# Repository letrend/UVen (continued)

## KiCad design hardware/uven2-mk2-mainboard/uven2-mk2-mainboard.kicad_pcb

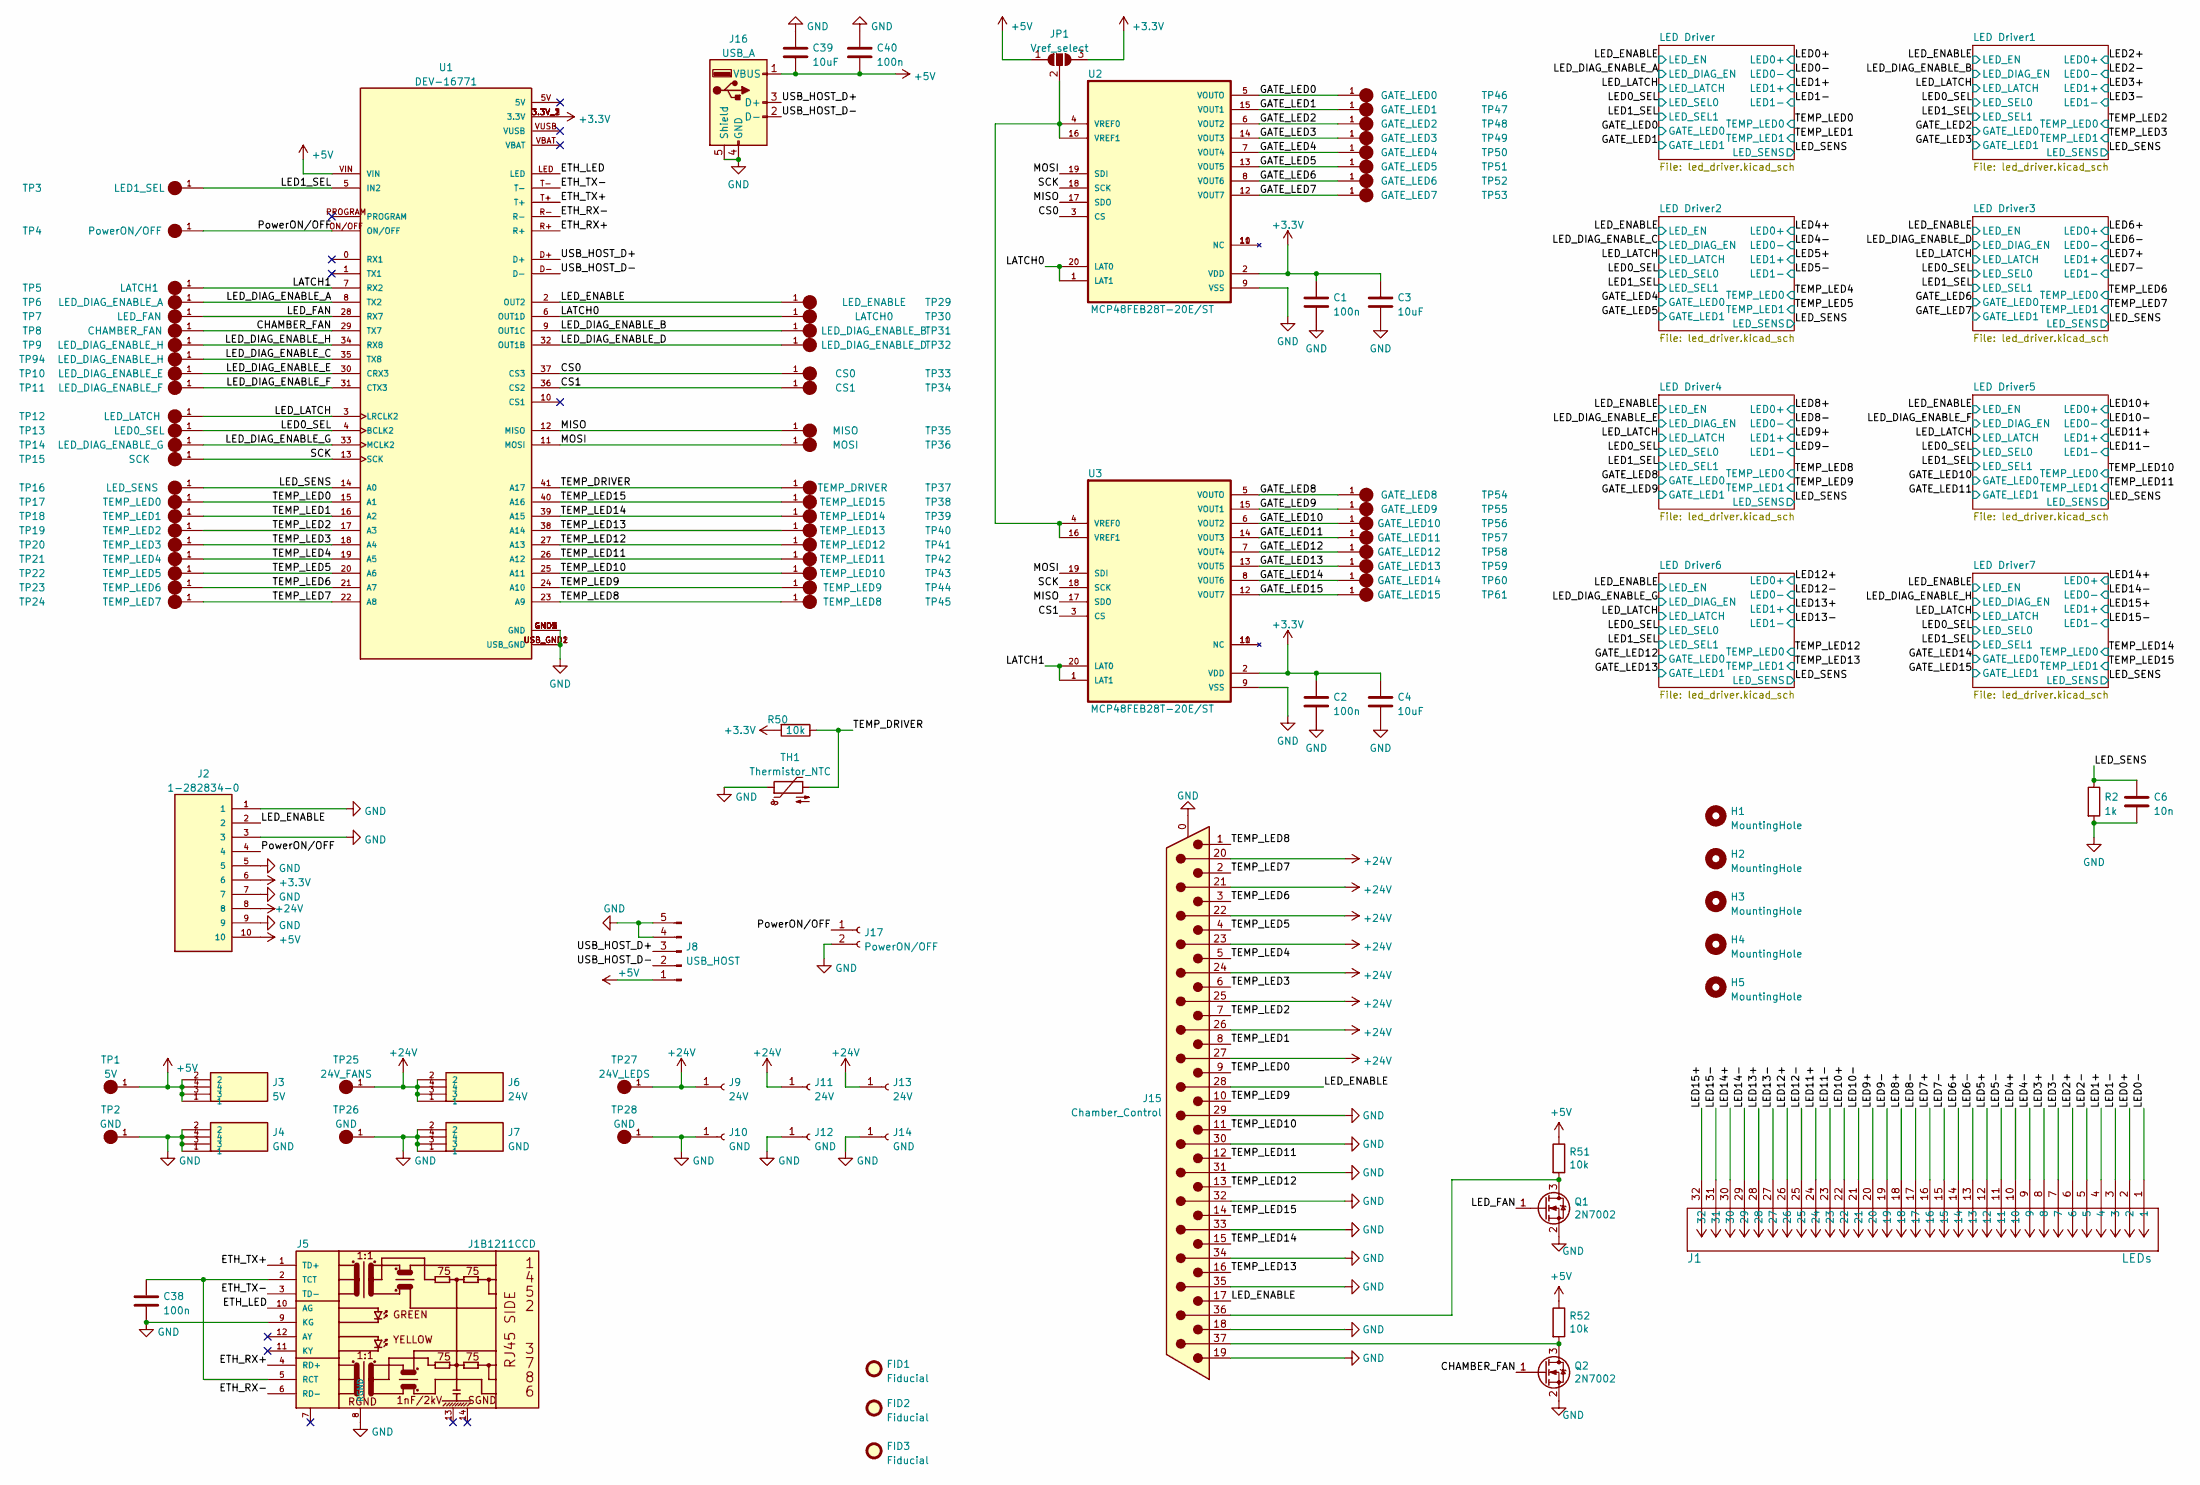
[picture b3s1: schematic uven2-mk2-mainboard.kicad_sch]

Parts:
C1, C2, C38, C40: 100n; C_0603_1608Metric_Pad1.08x0.95mm_HandSolder
C3, C4, C39: 10uF; C_0603_1608Metric_Pad1.08x0.95mm_HandSolder
C6: 10n; C_0603_1608Metric_Pad1.08x0.95mm_HandSolder
FID1, FID2, FID3: Fiducial; Fiducial_1mm_Dia_2.54mm_Outer_CopperTop
H1, H2, H3, H4, H5: MountingHole; MountingHole_3.2mm_M3
J1: LEDs; CONN_713-1436&slash_037-000_WAG
J2: 1-282834-0; TE_1-282834-0
J3: 5V; KEYSTONE_7767; PARTREV B
J4, J7: GND; KEYSTONE_7767; PARTREV B
J5: J1B1211CCD
J6: 24V; KEYSTONE_7767; PARTREV B
J8: USB_HOST; PinHeader_1x05_P2.54mm_Vertical
J9, J11, J13: 24V; 7466205R
J10, J12, J14: GND; 7466205R
J15: Chamber_Control; DSUB-37_Female_Horizontal_P2.77x2.84mm_EdgePinOffset7.70mm_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
J16: USB_A; USB_A_Molex_67643_Horizontal
J17: PowerON/OFF; PinHeader_1x02_P2.54mm_Vertical
JP1: Vref_select; SolderJumper-3_P1.3mm_Open_RoundedPad1.0x1.5mm_NumberLabels
Q1, Q2: 2N7002; SOT-23
R2: 1k; R_0603_1608Metric_Pad0.98x0.95mm_HandSolder
R50, R51, R52: 10k; R_0603_1608Metric_Pad0.98x0.95mm_HandSolder
TH1: Thermistor_NTC; R_0805_2012Metric_Pad1.20x1.40mm_HandSolder
TP1: 5V; TP420X150; PARTREV 1/06/14
TP2, TP26, TP28: GND; TP420X150; PARTREV 1/06/14
TP3: LED1_SEL; TP420X150; PARTREV 1/06/14
TP4: PowerON/OFF; TP420X150; PARTREV 1/06/14
TP5: LATCH1; TP420X150; PARTREV 1/06/14
TP6: LED_DIAG_ENABLE_A; TP420X150; PARTREV 1/06/14
TP7: LED_FAN; TP420X150; PARTREV 1/06/14
TP8: CHAMBER_FAN; TP420X150; PARTREV 1/06/14
TP9, TP94: LED_DIAG_ENABLE_H; TP420X150; PARTREV 1/06/14
TP10: LED_DIAG_ENABLE_E; TP420X150; PARTREV 1/06/14
TP11: LED_DIAG_ENABLE_F; TP420X150; PARTREV 1/06/14
TP12: LED_LATCH; TP420X150; PARTREV 1/06/14
TP13: LED0_SEL; TP420X150; PARTREV 1/06/14
TP14: LED_DIAG_ENABLE_G; TP420X150; PARTREV 1/06/14
TP15: SCK; TP420X150; PARTREV 1/06/14
TP16: LED_SENS; TP420X150; PARTREV 1/06/14
TP17: TEMP_LED0; TP420X150; PARTREV 1/06/14
TP18: TEMP_LED1; TP420X150; PARTREV 1/06/14
TP19: TEMP_LED2; TP420X150; PARTREV 1/06/14
TP20: TEMP_LED3; TP420X150; PARTREV 1/06/14
TP21: TEMP_LED4; TP420X150; PARTREV 1/06/14
TP22: TEMP_LED5; TP420X150; PARTREV 1/06/14
TP23: TEMP_LED6; TP420X150; PARTREV 1/06/14
TP24: TEMP_LED7; TP420X150; PARTREV 1/06/14
TP25: 24V_FANS; TP420X150; PARTREV 1/06/14
TP27: 24V_LEDS; TP420X150; PARTREV 1/06/14
TP29: LED_ENABLE; TP420X150; PARTREV 1/06/14
TP30: LATCH0; TP420X150; PARTREV 1/06/14
TP31: LED_DIAG_ENABLE_B; TP420X150; PARTREV 1/06/14
TP32: LED_DIAG_ENABLE_D; TP420X150; PARTREV 1/06/14
TP33: CS0; TP420X150; PARTREV 1/06/14
TP34: CS1; TP420X150; PARTREV 1/06/14
TP35: MISO; TP420X150; PARTREV 1/06/14
TP36: MOSI; TP420X150; PARTREV 1/06/14
TP37: TEMP_DRIVER; TP420X150; PARTREV 1/06/14
TP38: TEMP_LED15; TP420X150; PARTREV 1/06/14
TP39: TEMP_LED14; TP420X150; PARTREV 1/06/14
TP40: TEMP_LED13; TP420X150; PARTREV 1/06/14
TP41: TEMP_LED12; TP420X150; PARTREV 1/06/14
TP42: TEMP_LED11; TP420X150; PARTREV 1/06/14
TP43: TEMP_LED10; TP420X150; PARTREV 1/06/14
TP44: TEMP_LED9; TP420X150; PARTREV 1/06/14
TP45: TEMP_LED8; TP420X150; PARTREV 1/06/14
TP46: GATE_LED0; TP420X150; PARTREV 1/06/14
TP47: GATE_LED1; TP420X150; PARTREV 1/06/14
TP48: GATE_LED2; TP420X150; PARTREV 1/06/14
TP49: GATE_LED3; TP420X150; PARTREV 1/06/14
TP50: GATE_LED4; TP420X150; PARTREV 1/06/14
TP51: GATE_LED5; TP420X150; PARTREV 1/06/14
TP52: GATE_LED6; TP420X150; PARTREV 1/06/14
TP53: GATE_LED7; TP420X150; PARTREV 1/06/14
TP54: GATE_LED8; TP420X150; PARTREV 1/06/14
TP55: GATE_LED9; TP420X150; PARTREV 1/06/14
TP56: GATE_LED10; TP420X150; PARTREV 1/06/14
TP57: GATE_LED11; TP420X150; PARTREV 1/06/14
TP58: GATE_LED12; TP420X150; PARTREV 1/06/14
TP59: GATE_LED13; TP420X150; PARTREV 1/06/14
TP60: GATE_LED14; TP420X150; PARTREV 1/06/14
TP61: GATE_LED15; TP420X150; PARTREV 1/06/14
U1: DEV-16771; MODULE_DEV-16771; PARTREV 4.1
U2, U3: MCP48FEB28T-20E/ST; SOP65P640X120-20N

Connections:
+3.3V: C1.1, C2.1, C3.1, C4.1, J2.6, JP1.3 (B), R50.2, U1.3.3V_1 (3.3V), U1.3.3V_2 (3.3V), U1.3.3V_3 (3.3V), U2.2 (VDD), U3.2 (VDD); also elsewhere on the board
+5V: C39.2, C40.2, J2.10, J3.1, J3.2, J3.3, J3.4, J8.1, J16.1 (VBUS), JP1.1 (A), R51.1, R52.1, TP1.1, U1.VIN
+24V: J2.8, J6.1, J6.2, J6.3, J6.4, J9.1, J11.1, J13.1, J15.20, J15.21, J15.22, J15.23, J15.24, J15.25, J15.26, J15.27, TP25.1, TP27.1; also elsewhere on the board
/CHAMBER_FAN: Q2.1 (G), TP8.1, U1.29 (TX7)
/CS0: TP33.1, U1.37 (CS3), U2.3 (CS)
/CS1: TP34.1, U1.36 (CS2), U3.3 (CS)
/ETH_LED: J5.10 (AG), U1.LED
/ETH_RX+: J5.4 (RD+), U1.R+
/ETH_RX-: J5.6 (RD-), U1.R-
/ETH_TX+: J5.1 (TD+), U1.T+
/ETH_TX-: J5.3 (TD-), U1.T-
/GATE_LED0: TP46.1, U2.5 (VOUTO); also elsewhere on the board
/GATE_LED1: TP47.1, U2.15 (VOUT1); also elsewhere on the board
/GATE_LED2: TP48.1, U2.6 (VOUT2); also elsewhere on the board
/GATE_LED3: TP49.1, U2.14 (VOUT3); also elsewhere on the board
/GATE_LED4: TP50.1, U2.7 (VOUT4); also elsewhere on the board
/GATE_LED5: TP51.1, U2.13 (VOUT5); also elsewhere on the board
/GATE_LED6: TP52.1, U2.8 (VOUT6); also elsewhere on the board
/GATE_LED7: TP53.1, U2.12 (VOUT7); also elsewhere on the board
/GATE_LED8: TP54.1, U3.5 (VOUTO); also elsewhere on the board
/GATE_LED9: TP55.1, U3.15 (VOUT1); also elsewhere on the board
/GATE_LED10: TP56.1, U3.6 (VOUT2); also elsewhere on the board
/GATE_LED11: TP57.1, U3.14 (VOUT3); also elsewhere on the board
/GATE_LED12: TP58.1, U3.7 (VOUT4); also elsewhere on the board
/GATE_LED13: TP59.1, U3.13 (VOUT5); also elsewhere on the board
/GATE_LED14: TP60.1, U3.8 (VOUT6); also elsewhere on the board
/GATE_LED15: TP61.1, U3.12 (VOUT7); also elsewhere on the board
/LATCH0: TP30.1, U1.6 (OUT1D), U2.1 (LAT1), U2.20 (LAT0)
/LATCH1: TP5.1, U1.7 (RX2), U3.1 (LAT1), U3.20 (LAT0)
/LED0+: J1.2; also elsewhere on the board
/LED0-: J1.1; also elsewhere on the board
/LED0_SEL: TP13.1, U1.4 (BCLK2); also elsewhere on the board
/LED1+: J1.4; also elsewhere on the board
/LED1-: J1.3; also elsewhere on the board
/LED1_SEL: TP3.1, U1.5 (IN2); also elsewhere on the board
/LED2+: J1.6; also elsewhere on the board
/LED2-: J1.5; also elsewhere on the board
/LED3+: J1.8; also elsewhere on the board
/LED3-: J1.7; also elsewhere on the board
/LED4+: J1.10; also elsewhere on the board
/LED4-: J1.9; also elsewhere on the board
/LED5+: J1.12; also elsewhere on the board
/LED5-: J1.11; also elsewhere on the board
/LED6+: J1.14; also elsewhere on the board
/LED6-: J1.13; also elsewhere on the board
/LED7+: J1.16; also elsewhere on the board
/LED7-: J1.15; also elsewhere on the board
/LED8+: J1.18; also elsewhere on the board
/LED8-: J1.17; also elsewhere on the board
/LED9+: J1.20; also elsewhere on the board
/LED9-: J1.19; also elsewhere on the board
/LED10+: J1.22; also elsewhere on the board
/LED10-: J1.21; also elsewhere on the board
/LED11+: J1.24; also elsewhere on the board
/LED11-: J1.23; also elsewhere on the board
/LED12+: J1.26; also elsewhere on the board
/LED12-: J1.25; also elsewhere on the board
/LED13+: J1.28; also elsewhere on the board
/LED13-: J1.27; also elsewhere on the board
/LED14+: J1.30; also elsewhere on the board
/LED14-: J1.29; also elsewhere on the board
/LED15+: J1.32; also elsewhere on the board
/LED15-: J1.31; also elsewhere on the board
/LED_DIAG_ENABLE_A: TP6.1, U1.8 (TX2); also elsewhere on the board
/LED_DIAG_ENABLE_B: TP31.1, U1.9 (OUT1C); also elsewhere on the board
/LED_DIAG_ENABLE_C: TP94.1, U1.35 (TX8); also elsewhere on the board
/LED_DIAG_ENABLE_D: TP32.1, U1.32 (OUT1B); also elsewhere on the board
/LED_DIAG_ENABLE_E: TP10.1, U1.30 (CRX3); also elsewhere on the board
/LED_DIAG_ENABLE_F: TP11.1, U1.31 (CTX3); also elsewhere on the board
/LED_DIAG_ENABLE_G: TP14.1, U1.33 (MCLK2); also elsewhere on the board
/LED_DIAG_ENABLE_H: TP9.1, U1.34 (RX8); also elsewhere on the board
/LED_ENABLE: J2.2, J15.17, J15.28, TP29.1, U1.2 (OUT2); also elsewhere on the board
/LED_FAN: Q1.1 (G), TP7.1, U1.28 (RX7)
/LED_LATCH: TP12.1, U1.3 (LRCLK2); also elsewhere on the board
/LED_SENS: C6.1, R2.1, TP16.1, U1.14 (A0); also elsewhere on the board
/MISO: TP35.1, U1.12 (MISO), U2.17 (SDO), U3.17 (SDO)
/MOSI: TP36.1, U1.11 (MOSI), U2.19 (SDI), U3.19 (SDI)
/PowerON/OFF: J2.4, J17.1, TP4.1, U1.ON/OFF
/SCK: TP15.1, U1.13 (SCK), U2.18 (SCK), U3.18 (SCK)
/TEMP_DRIVER: R50.1, TH1.2, TP37.1, U1.41 (A17)
/TEMP_LED0: J15.9, TP17.1, U1.15 (A1); also elsewhere on the board
/TEMP_LED1: J15.8, TP18.1, U1.16 (A2); also elsewhere on the board
/TEMP_LED2: J15.7, TP19.1, U1.17 (A3); also elsewhere on the board
/TEMP_LED3: J15.6, TP20.1, U1.18 (A4); also elsewhere on the board
/TEMP_LED4: J15.5, TP21.1, U1.19 (A5); also elsewhere on the board
/TEMP_LED5: J15.4, TP22.1, U1.20 (A6); also elsewhere on the board
/TEMP_LED6: J15.3, TP23.1, U1.21 (A7); also elsewhere on the board
/TEMP_LED7: J15.2, TP24.1, U1.22 (A8); also elsewhere on the board
/TEMP_LED8: J15.1, TP45.1, U1.23 (A9); also elsewhere on the board
/TEMP_LED9: J15.10, TP44.1, U1.24 (A10); also elsewhere on the board
/TEMP_LED10: J15.11, TP43.1, U1.25 (A11); also elsewhere on the board
/TEMP_LED11: J15.12, TP42.1, U1.26 (A12); also elsewhere on the board
/TEMP_LED12: J15.13, TP41.1, U1.27 (A13); also elsewhere on the board
/TEMP_LED13: J15.16, TP40.1, U1.38 (A14); also elsewhere on the board
/TEMP_LED14: J15.15, TP39.1, U1.39 (A15); also elsewhere on the board
/TEMP_LED15: J15.14, TP38.1, U1.40 (A16); also elsewhere on the board
/USB_HOST_D+: J8.3, J16.3 (D+), U1.D+
/USB_HOST_D-: J8.2, J16.2 (D-), U1.D-
GND: C1.2, C2.2, C3.2, C4.2, C6.2, C38.2, C39.1, C40.1, J2.1, J2.3, J2.5, J2.7, J2.9, J4.1, J4.2, J4.3, J4.4, J5.8 (RGND), J5.9 (KG), J7.1, J7.2, J7.3, J7.4, J8.4, J8.5, J10.1, J12.1, J14.1, J15.0 (PAD), J15.18, J15.19, J15.29, J15.30, J15.31, J15.32, J15.33, J15.34, J15.35, J16.4 (GND), J16.5 (Shield), J17.2, Q1.2 (S), Q2.2 (S), R2.2, TH1.1, TP2.1, TP26.1, TP28.1, U1.GND1 (GND), U1.GND2 (GND), U1.GND3 (GND), U1.GND4 (GND), U1.GND5 (GND), U1.USB_GND1 (USB_GND), U1.USB_GND2 (USB_GND), U2.9 (VSS), U3.9 (VSS); also elsewhere on the board
unnamed: C38.1, J5.2 (TCT), J5.5 (RCT)
unnamed: JP1.2 (C), U2.4 (VREF0), U2.16 (VREF1), U3.4 (VREF0), U3.16 (VREF1)
unnamed: J15.36, Q1.3 (D), R51.2
unnamed: J15.37, Q2.3 (D), R52.2

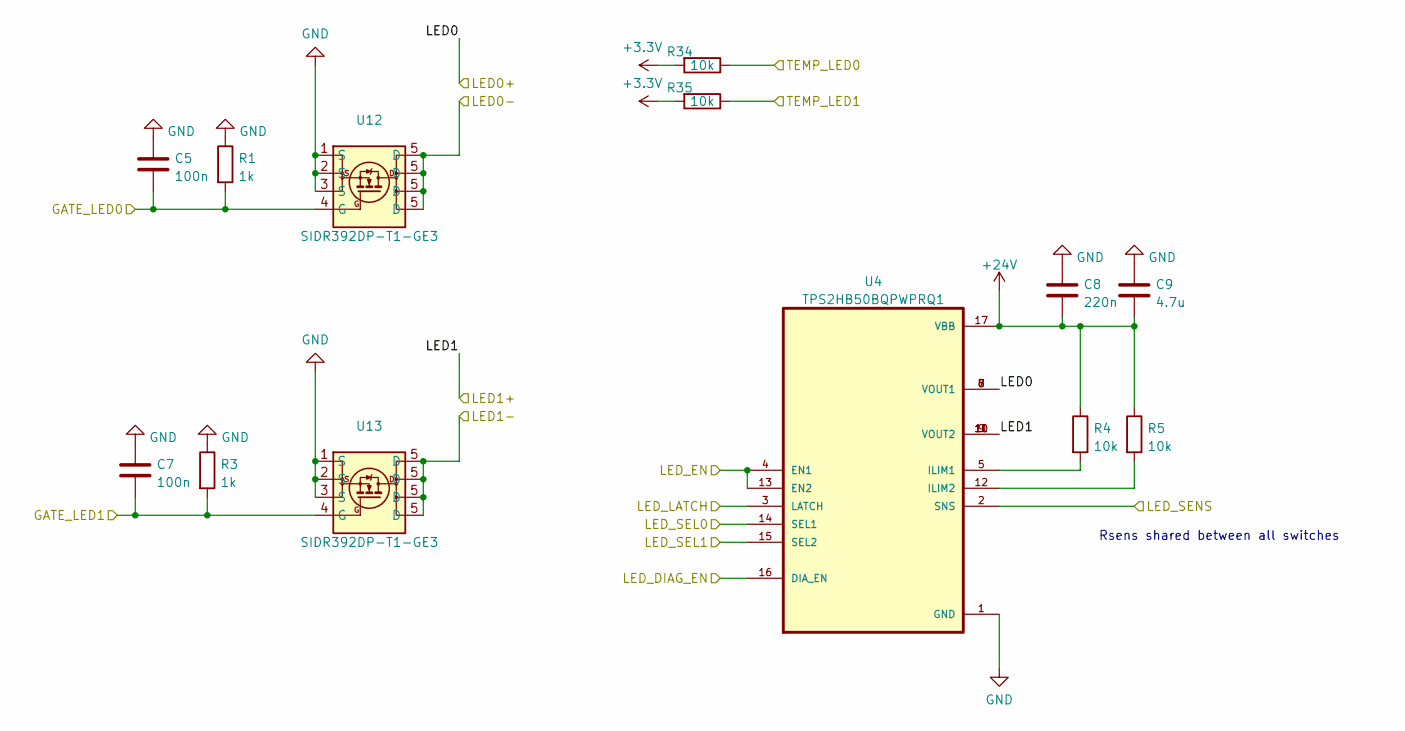
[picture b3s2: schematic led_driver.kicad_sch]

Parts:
C5, C7: 100n; C_0603_1608Metric_Pad1.08x0.95mm_HandSolder
C8: 220n; C_0603_1608Metric_Pad1.08x0.95mm_HandSolder
C9: 4.7u; C_0603_1608Metric_Pad1.08x0.95mm_HandSolder
R1, R3: 1k; R_0603_1608Metric_Pad0.98x0.95mm_HandSolder
R4, R5, R34, R35: 10k; R_0603_1608Metric_Pad0.98x0.95mm_HandSolder
U4: TPS2HB50BQPWPRQ1; SOP65P640X120-17N
U12, U13: SIDR392DP-T1-GE3; PowerPAK SO-8DC

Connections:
+3.3V: R34.2, R35.2; also elsewhere on the board
+24V: C8.2, C9.2, R4.1, R5.1, U4.17 (VBB); also elsewhere on the board
/GATE_LED0: C5.2, R1.2, U12.4 (G); also elsewhere on the board
/GATE_LED1: C7.2, R3.2, U13.4 (G); also elsewhere on the board
/LED0+: U4.6 (VOUT1), U4.7 (VOUT1), U4.8 (VOUT1); also elsewhere on the board
/LED0-: U12.5 (D); also elsewhere on the board
/LED0_SEL: U4.14 (SEL1); also elsewhere on the board
/LED1+: U4.9 (VOUT2), U4.10 (VOUT2), U4.11 (VOUT2); also elsewhere on the board
/LED1-: U13.5 (D); also elsewhere on the board
/LED1_SEL: U4.15 (SEL2); also elsewhere on the board
/LED_DIAG_ENABLE_A: U4.16 (DIA_EN); also elsewhere on the board
/LED_ENABLE: U4.4 (EN1), U4.13 (EN2); also elsewhere on the board
/LED_LATCH: U4.3 (LATCH); also elsewhere on the board
/LED_SENS: U4.2 (SNS); also elsewhere on the board
/TEMP_LED0: R34.1; also elsewhere on the board
/TEMP_LED1: R35.1; also elsewhere on the board
GND: C5.1, C7.1, C8.1, C9.1, R1.1, R3.1, U4.1 (GND), U12.1 (S), U12.2 (S), U12.3 (S), U13.1 (S), U13.2 (S), U13.3 (S); also elsewhere on the board
unnamed: R4.2, U4.5 (ILIM1)
unnamed: R5.2, U4.12 (ILIM2)

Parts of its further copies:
C10, C11, C14, C15, C18, C19, C22, C23, C26, C27, C30, C31, C34, C35: 100n; C_0603_1608Metric_Pad1.08x0.95mm_HandSolder
C12, C16, C20, C24, C28, C32, C36: 220n; C_0603_1608Metric_Pad1.08x0.95mm_HandSolder
C13, C17, C21, C25, C29, C33, C37: 4.7u; C_0603_1608Metric_Pad1.08x0.95mm_HandSolder
R6, R7, R10, R11, R14, R15, R18, R19, R22, R23, R26, R27, R30, R31: 1k; R_0603_1608Metric_Pad0.98x0.95mm_HandSolder
R8, R9, R12, R13, R16, R17, R20, R21, R24, R25, R28, R29, R32, R33, R36, R37, R38, R39, R40, R41, R42, R43, R44, R45, R46, R47, R48, R49: 10k; R_0603_1608Metric_Pad0.98x0.95mm_HandSolder
U5, U6, U7, U8, U9, U10, U11: TPS2HB50BQPWPRQ1; SOP65P640X120-17N
U14, U15, U16, U17, U18, U19, U20, U21, U22, U23, U24, U25, U26, U27: SIDR392DP-T1-GE3; PowerPAK SO-8DC

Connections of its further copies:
+3.3V: R36.2, R37.2, R38.2, R39.2, R40.2, R41.2, R42.2, R43.2, R44.2, R45.2, R46.2, R47.2, R48.2, R49.2; also elsewhere on the board
+24V: C12.2, C13.2, C16.2, C17.2, C20.2, C21.2, C24.2, C25.2, C28.2, C29.2, C32.2, C33.2, C36.2, C37.2, R8.1, R9.1, R12.1, R13.1, R16.1, R17.1, R20.1, R21.1, R24.1, R25.1, R28.1, R29.1, R32.1, R33.1, U5.17 (VBB), U6.17 (VBB), U7.17 (VBB), U8.17 (VBB), U9.17 (VBB), U10.17 (VBB), U11.17 (VBB); also elsewhere on the board
/GATE_LED2: C10.2, R6.2, U14.4 (G); also elsewhere on the board
/GATE_LED3: C11.2, R7.2, U15.4 (G); also elsewhere on the board
/GATE_LED4: C14.2, R10.2, U16.4 (G); also elsewhere on the board
/GATE_LED5: C15.2, R11.2, U17.4 (G); also elsewhere on the board
/GATE_LED6: C18.2, R14.2, U18.4 (G); also elsewhere on the board
/GATE_LED7: C19.2, R15.2, U19.4 (G); also elsewhere on the board
/GATE_LED8: C22.2, R18.2, U20.4 (G); also elsewhere on the board
/GATE_LED9: C23.2, R19.2, U21.4 (G); also elsewhere on the board
/GATE_LED10: C26.2, R22.2, U22.4 (G); also elsewhere on the board
/GATE_LED11: C27.2, R23.2, U23.4 (G); also elsewhere on the board
/GATE_LED12: C30.2, R26.2, U24.4 (G); also elsewhere on the board
/GATE_LED13: C31.2, R27.2, U25.4 (G); also elsewhere on the board
/GATE_LED14: C34.2, R30.2, U26.4 (G); also elsewhere on the board
/GATE_LED15: C35.2, R31.2, U27.4 (G); also elsewhere on the board
/LED0_SEL: U5.14 (SEL1), U6.14 (SEL1), U7.14 (SEL1), U8.14 (SEL1), U9.14 (SEL1), U10.14 (SEL1), U11.14 (SEL1); also elsewhere on the board
/LED1_SEL: U5.15 (SEL2), U6.15 (SEL2), U7.15 (SEL2), U8.15 (SEL2), U9.15 (SEL2), U10.15 (SEL2), U11.15 (SEL2); also elsewhere on the board
/LED2+: U5.6 (VOUT1), U5.7 (VOUT1), U5.8 (VOUT1); also elsewhere on the board
/LED2-: U14.5 (D); also elsewhere on the board
/LED3+: U5.9 (VOUT2), U5.10 (VOUT2), U5.11 (VOUT2); also elsewhere on the board
/LED3-: U15.5 (D); also elsewhere on the board
/LED4+: U6.6 (VOUT1), U6.7 (VOUT1), U6.8 (VOUT1); also elsewhere on the board
/LED4-: U16.5 (D); also elsewhere on the board
/LED5+: U6.9 (VOUT2), U6.10 (VOUT2), U6.11 (VOUT2); also elsewhere on the board
/LED5-: U17.5 (D); also elsewhere on the board
/LED6+: U7.6 (VOUT1), U7.7 (VOUT1), U7.8 (VOUT1); also elsewhere on the board
/LED6-: U18.5 (D); also elsewhere on the board
/LED7+: U7.9 (VOUT2), U7.10 (VOUT2), U7.11 (VOUT2); also elsewhere on the board
/LED7-: U19.5 (D); also elsewhere on the board
/LED8+: U8.6 (VOUT1), U8.7 (VOUT1), U8.8 (VOUT1); also elsewhere on the board
/LED8-: U20.5 (D); also elsewhere on the board
/LED9+: U8.9 (VOUT2), U8.10 (VOUT2), U8.11 (VOUT2); also elsewhere on the board
/LED9-: U21.5 (D); also elsewhere on the board
/LED10+: U9.6 (VOUT1), U9.7 (VOUT1), U9.8 (VOUT1); also elsewhere on the board
/LED10-: U22.5 (D); also elsewhere on the board
/LED11+: U9.9 (VOUT2), U9.10 (VOUT2), U9.11 (VOUT2); also elsewhere on the board
/LED11-: U23.5 (D); also elsewhere on the board
/LED12+: U10.6 (VOUT1), U10.7 (VOUT1), U10.8 (VOUT1); also elsewhere on the board
/LED12-: U24.5 (D); also elsewhere on the board
/LED13+: U10.9 (VOUT2), U10.10 (VOUT2), U10.11 (VOUT2); also elsewhere on the board
/LED13-: U25.5 (D); also elsewhere on the board
/LED14+: U11.6 (VOUT1), U11.7 (VOUT1), U11.8 (VOUT1); also elsewhere on the board
/LED14-: U26.5 (D); also elsewhere on the board
/LED15+: U11.9 (VOUT2), U11.10 (VOUT2), U11.11 (VOUT2); also elsewhere on the board
/LED15-: U27.5 (D); also elsewhere on the board
/LED_DIAG_ENABLE_B: U5.16 (DIA_EN); also elsewhere on the board
/LED_DIAG_ENABLE_C: U6.16 (DIA_EN); also elsewhere on the board
/LED_DIAG_ENABLE_D: U7.16 (DIA_EN); also elsewhere on the board
/LED_DIAG_ENABLE_E: U8.16 (DIA_EN); also elsewhere on the board
/LED_DIAG_ENABLE_F: U9.16 (DIA_EN); also elsewhere on the board
/LED_DIAG_ENABLE_G: U10.16 (DIA_EN); also elsewhere on the board
/LED_DIAG_ENABLE_H: U11.16 (DIA_EN); also elsewhere on the board
/LED_ENABLE: U5.4 (EN1), U5.13 (EN2), U6.4 (EN1), U6.13 (EN2), U7.4 (EN1), U7.13 (EN2), U8.4 (EN1), U8.13 (EN2), U9.4 (EN1), U9.13 (EN2), U10.4 (EN1), U10.13 (EN2), U11.4 (EN1), U11.13 (EN2); also elsewhere on the board
/LED_LATCH: U5.3 (LATCH), U6.3 (LATCH), U7.3 (LATCH), U8.3 (LATCH), U9.3 (LATCH), U10.3 (LATCH), U11.3 (LATCH); also elsewhere on the board
/LED_SENS: U5.2 (SNS), U6.2 (SNS), U7.2 (SNS), U8.2 (SNS), U9.2 (SNS), U10.2 (SNS), U11.2 (SNS); also elsewhere on the board
/TEMP_LED2: R36.1; also elsewhere on the board
/TEMP_LED3: R37.1; also elsewhere on the board
/TEMP_LED4: R38.1; also elsewhere on the board
/TEMP_LED5: R39.1; also elsewhere on the board
/TEMP_LED6: R40.1; also elsewhere on the board
/TEMP_LED7: R41.1; also elsewhere on the board
/TEMP_LED8: R42.1; also elsewhere on the board
/TEMP_LED9: R43.1; also elsewhere on the board
/TEMP_LED10: R44.1; also elsewhere on the board
/TEMP_LED11: R45.1; also elsewhere on the board
/TEMP_LED12: R46.1; also elsewhere on the board
/TEMP_LED13: R47.1; also elsewhere on the board
/TEMP_LED14: R48.1; also elsewhere on the board
/TEMP_LED15: R49.1; also elsewhere on the board
GND: C10.1, C11.1, C12.1, C13.1, C14.1, C15.1, C16.1, C17.1, C18.1, C19.1, C20.1, C21.1, C22.1, C23.1, C24.1, C25.1, C26.1, C27.1, C28.1, C29.1, C30.1, C31.1, C32.1, C33.1, C34.1, C35.1, C36.1, C37.1, R6.1, R7.1, R10.1, R11.1, R14.1, R15.1, R18.1, R19.1, R22.1, R23.1, R26.1, R27.1, R30.1, R31.1, U5.1 (GND), U6.1 (GND), U7.1 (GND), U8.1 (GND), U9.1 (GND), U10.1 (GND), U11.1 (GND), U14.1 (S), U14.2 (S), U14.3 (S), U15.1 (S), U15.2 (S), U15.3 (S), U16.1 (S), U16.2 (S), U16.3 (S), U17.1 (S), U17.2 (S), U17.3 (S), U18.1 (S), U18.2 (S), U18.3 (S), U19.1 (S), U19.2 (S), U19.3 (S), U20.1 (S), U20.2 (S), U20.3 (S), U21.1 (S), U21.2 (S), U21.3 (S), U22.1 (S), U22.2 (S), U22.3 (S), U23.1 (S), U23.2 (S), U23.3 (S), U24.1 (S), U24.2 (S), U24.3 (S), U25.1 (S), U25.2 (S), U25.3 (S), U26.1 (S), U26.2 (S), U26.3 (S), U27.1 (S), U27.2 (S), U27.3 (S); also elsewhere on the board
unnamed: R8.2, U5.5 (ILIM1)
unnamed: R9.2, U5.12 (ILIM2)
unnamed: R12.2, U6.5 (ILIM1)
unnamed: R13.2, U6.12 (ILIM2)
unnamed: R16.2, U7.5 (ILIM1)
unnamed: R17.2, U7.12 (ILIM2)
unnamed: R20.2, U8.5 (ILIM1)
unnamed: R21.2, U8.12 (ILIM2)
unnamed: R24.2, U9.5 (ILIM1)
unnamed: R25.2, U9.12 (ILIM2)
unnamed: R28.2, U10.5 (ILIM1)
unnamed: R29.2, U10.12 (ILIM2)
unnamed: R32.2, U11.5 (ILIM1)
unnamed: R33.2, U11.12 (ILIM2)

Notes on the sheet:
Rsens shared between all switches

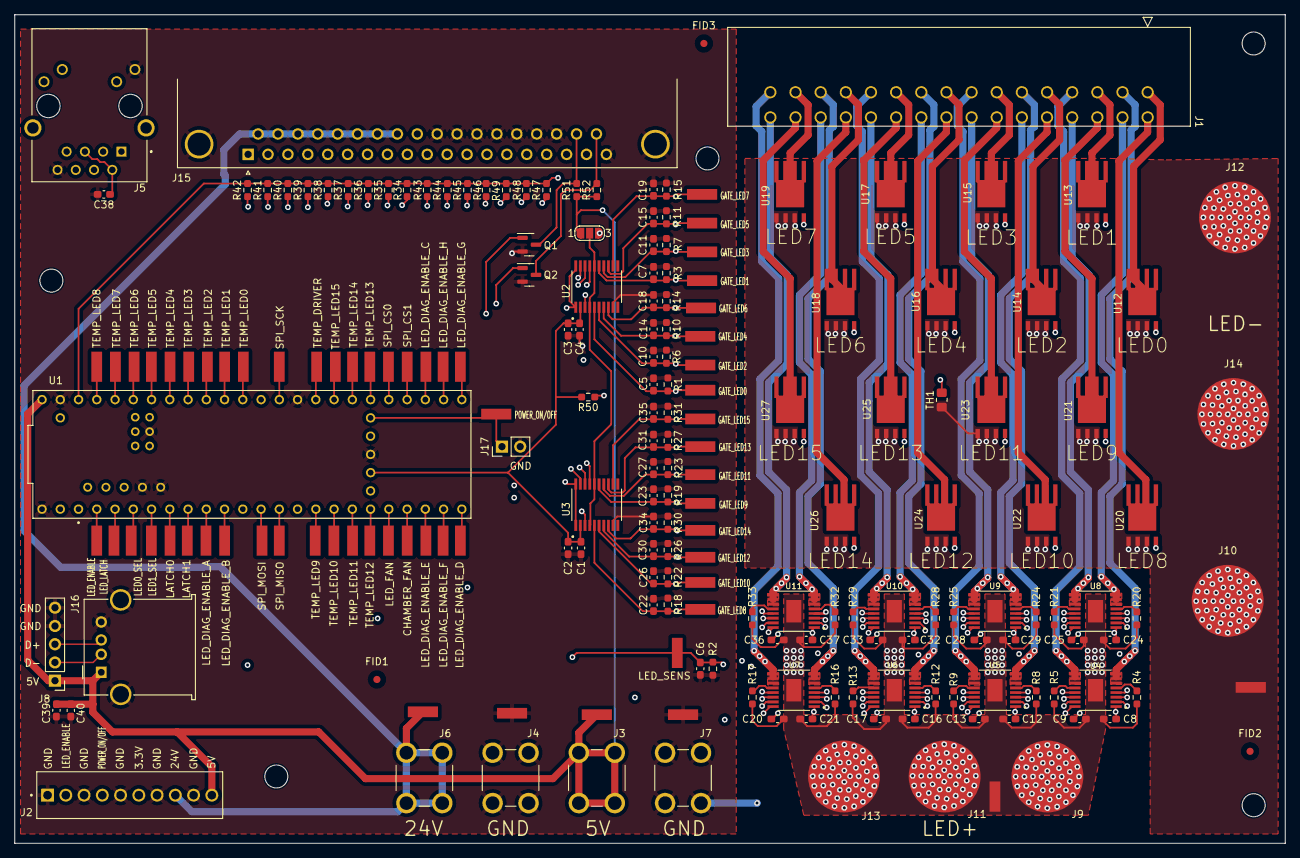
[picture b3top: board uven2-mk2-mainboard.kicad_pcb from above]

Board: 4 copper layers, 176.8 x 115.3 mm, 210 parts (0 on the bottom side), 119 nets.

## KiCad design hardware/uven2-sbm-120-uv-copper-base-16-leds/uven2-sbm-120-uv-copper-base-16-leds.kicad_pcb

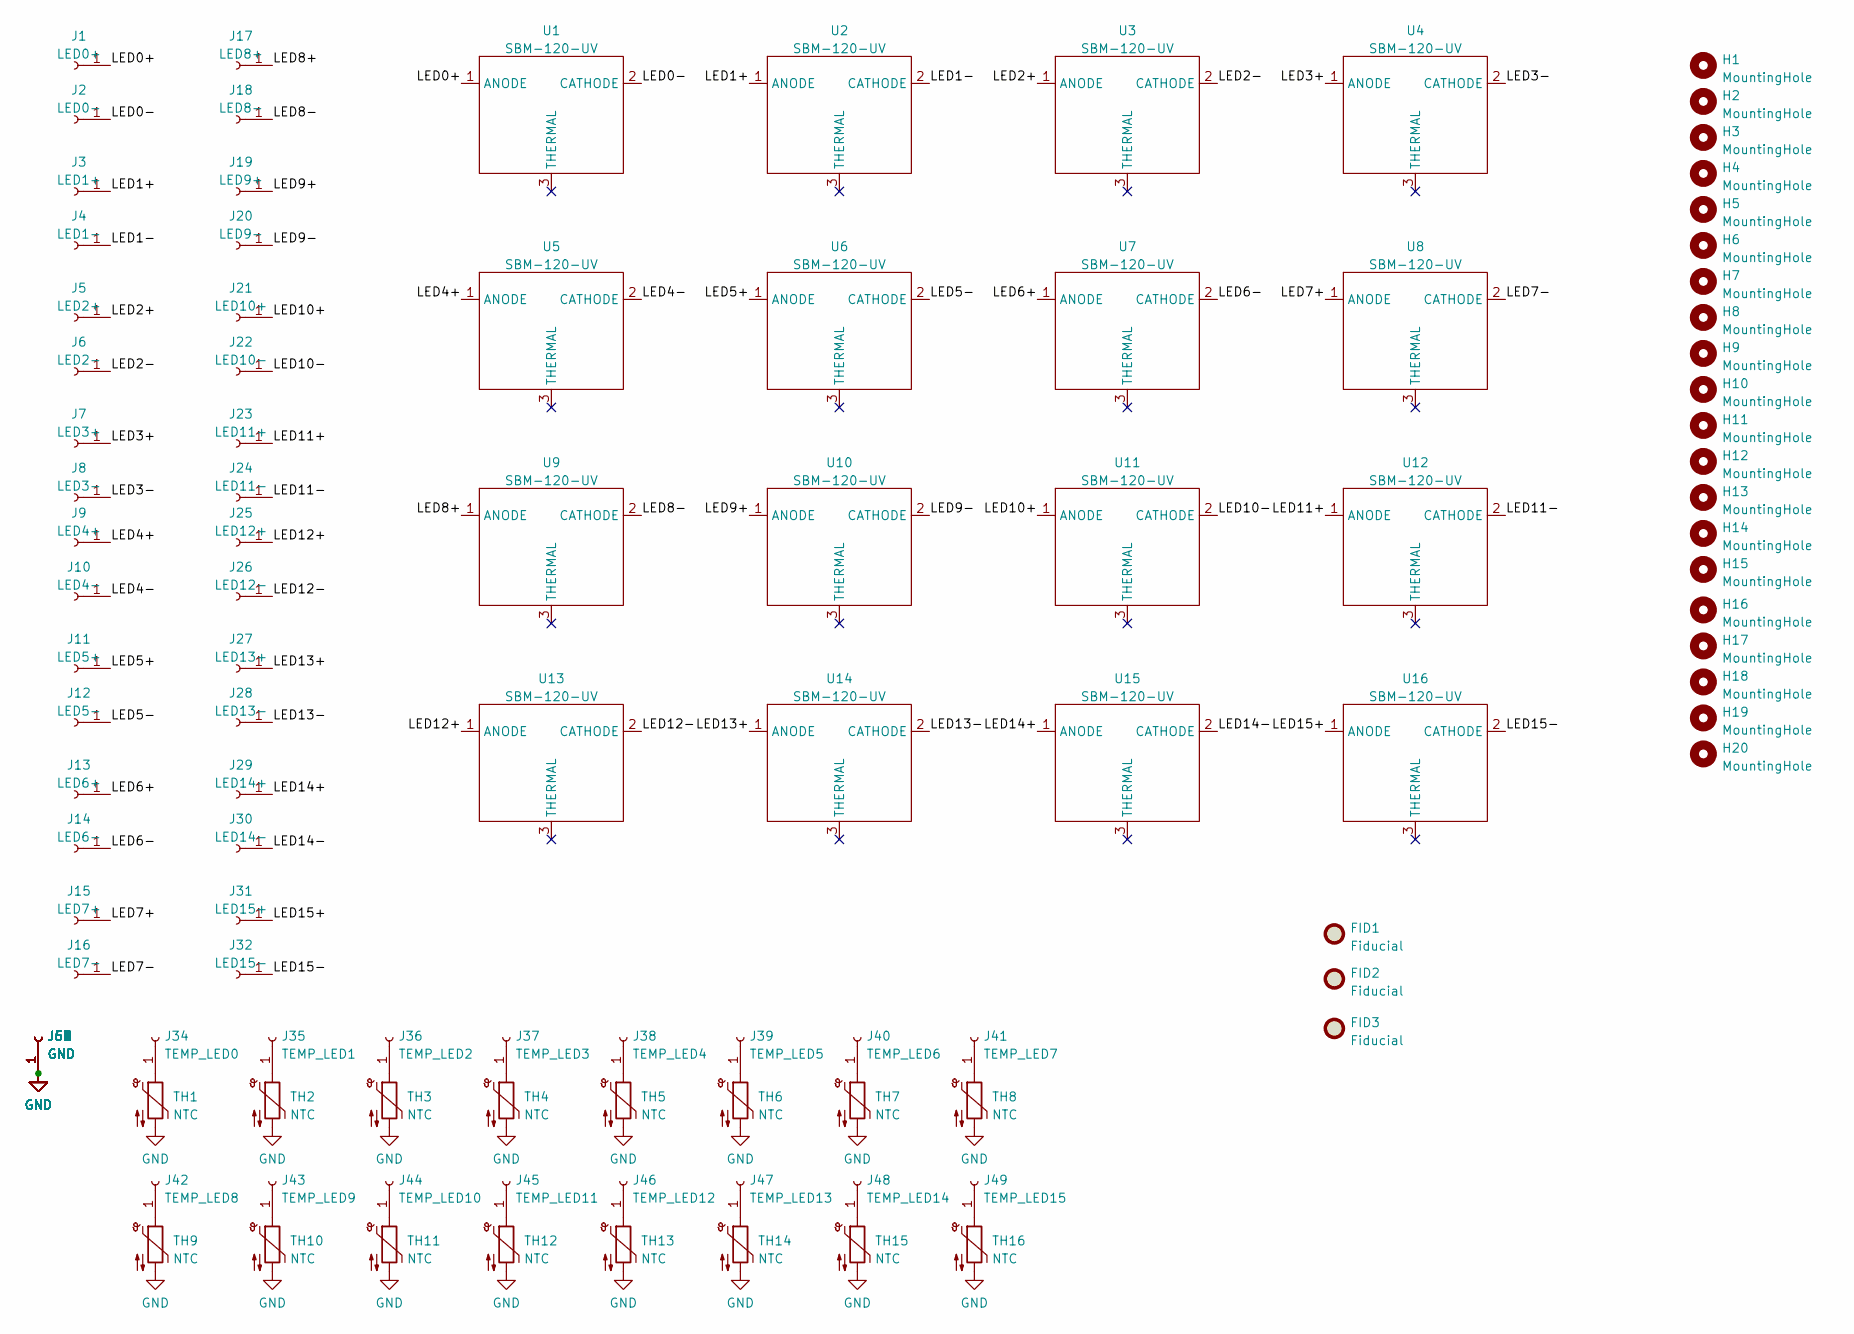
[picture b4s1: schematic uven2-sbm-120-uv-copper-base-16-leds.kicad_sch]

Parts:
FID1, FID2, FID3: Fiducial; Fiducial_1mm_Dia_2.54mm_Outer_CopperTop
H1, H2, H3, H4, H5, H6, H7, H8, H9, H10, H11, H12, H13, H14, H15, H16, H17, H18, H19, H20: MountingHole; MountingHole_3.2mm_M3
J1: LED0+; TestPoint_Pad_3.0x3.0mm
J2: LED0-; TestPoint_Pad_3.0x3.0mm
J3: LED1+; TestPoint_Pad_3.0x3.0mm
J4: LED1-; TestPoint_Pad_3.0x3.0mm
J5: LED2+; TestPoint_Pad_3.0x3.0mm
J6: LED2-; TestPoint_Pad_3.0x3.0mm
J7: LED3+; TestPoint_Pad_3.0x3.0mm
J8: LED3-; TestPoint_Pad_3.0x3.0mm
J9: LED4+; TestPoint_Pad_3.0x3.0mm
J10: LED4-; TestPoint_Pad_3.0x3.0mm
J11: LED5+; TestPoint_Pad_3.0x3.0mm
J12: LED5-; TestPoint_Pad_3.0x3.0mm
J13: LED6+; TestPoint_Pad_3.0x3.0mm
J14: LED6-; TestPoint_Pad_3.0x3.0mm
J15: LED7+; TestPoint_Pad_3.0x3.0mm
J16: LED7-; TestPoint_Pad_3.0x3.0mm
J17: LED8+; TestPoint_Pad_3.0x3.0mm
J18: LED8-; TestPoint_Pad_3.0x3.0mm
J19: LED9+; TestPoint_Pad_3.0x3.0mm
J20: LED9-; TestPoint_Pad_3.0x3.0mm
J21: LED10+; TestPoint_Pad_3.0x3.0mm
J22: LED10-; TestPoint_Pad_3.0x3.0mm
J23: LED11+; TestPoint_Pad_3.0x3.0mm
J24: LED11-; TestPoint_Pad_3.0x3.0mm
J25: LED12+; TestPoint_Pad_3.0x3.0mm
J26: LED12-; TestPoint_Pad_3.0x3.0mm
J27: LED13+; TestPoint_Pad_3.0x3.0mm
J28: LED13-; TestPoint_Pad_3.0x3.0mm
J29: LED14+; TestPoint_Pad_3.0x3.0mm
J30: LED14-; TestPoint_Pad_3.0x3.0mm
J31: LED15+; TestPoint_Pad_3.0x3.0mm
J32: LED15-; TestPoint_Pad_3.0x3.0mm
J34: TEMP_LED0; TestPoint_Pad_2.0x2.0mm
J35: TEMP_LED1; TestPoint_Pad_2.0x2.0mm
J36: TEMP_LED2; TestPoint_Pad_2.0x2.0mm
J37: TEMP_LED3; TestPoint_Pad_2.0x2.0mm
J38: TEMP_LED4; TestPoint_Pad_2.0x2.0mm
J39: TEMP_LED5; TestPoint_Pad_2.0x2.0mm
J40: TEMP_LED6; TestPoint_Pad_2.0x2.0mm
J41: TEMP_LED7; TestPoint_Pad_2.0x2.0mm
J42: TEMP_LED8; TestPoint_Pad_2.0x2.0mm
J43: TEMP_LED9; TestPoint_Pad_2.0x2.0mm
J44: TEMP_LED10; TestPoint_Pad_2.0x2.0mm
J45: TEMP_LED11; TestPoint_Pad_2.0x2.0mm
J46: TEMP_LED12; TestPoint_Pad_2.0x2.0mm
J47: TEMP_LED13; TestPoint_Pad_2.0x2.0mm
J48: TEMP_LED14; TestPoint_Pad_2.0x2.0mm
J49: TEMP_LED15; TestPoint_Pad_2.0x2.0mm
J50, J51, J52, J53, J54, J55, J56, J57, J58, J59, J60, J61, J62, J63, J64, J65: GND; TestPoint_Pad_2.0x2.0mm
TH1, TH2, TH3, TH4, TH5, TH6, TH7, TH8, TH9, TH10, TH11, TH12, TH13, TH14, TH15, TH16: NTC; R_0805_2012Metric_Pad1.20x1.40mm_HandSolder
U1, U2, U3, U4, U5, U6, U7, U8, U9, U10, U11, U12, U13, U14, U15, U16: SBM-120-UV

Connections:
/LED0+: J1.1, U1.1 (ANODE)
/LED0-: J2.1, U1.2 (CATHODE)
/LED1+: J3.1, U2.1 (ANODE)
/LED1-: J4.1, U2.2 (CATHODE)
/LED2+: J5.1, U3.1 (ANODE)
/LED2-: J6.1, U3.2 (CATHODE)
/LED3+: J7.1, U4.1 (ANODE)
/LED3-: J8.1, U4.2 (CATHODE)
/LED4+: J9.1, U5.1 (ANODE)
/LED4-: J10.1, U5.2 (CATHODE)
/LED5+: J11.1, U6.1 (ANODE)
/LED5-: J12.1, U6.2 (CATHODE)
/LED6+: J13.1, U7.1 (ANODE)
/LED6-: J14.1, U7.2 (CATHODE)
/LED7+: J15.1, U8.1 (ANODE)
/LED7-: J16.1, U8.2 (CATHODE)
/LED8+: J17.1, U9.1 (ANODE)
/LED8-: J18.1, U9.2 (CATHODE)
/LED9+: J19.1, U10.1 (ANODE)
/LED9-: J20.1, U10.2 (CATHODE)
/LED10+: J21.1, U11.1 (ANODE)
/LED10-: J22.1, U11.2 (CATHODE)
/LED11+: J23.1, U12.1 (ANODE)
/LED11-: J24.1, U12.2 (CATHODE)
/LED12+: J25.1, U13.1 (ANODE)
/LED12-: J26.1, U13.2 (CATHODE)
/LED13+: J27.1, U14.1 (ANODE)
/LED13-: J28.1, U14.2 (CATHODE)
/LED14+: J29.1, U15.1 (ANODE)
/LED14-: J30.1, U15.2 (CATHODE)
/LED15+: J31.1, U16.1 (ANODE)
/LED15-: J32.1, U16.2 (CATHODE)
GND: J50.1, J51.1, J52.1, J53.1, J54.1, J55.1, J56.1, J57.1, J58.1, J59.1, J60.1, J61.1, J62.1, J63.1, J64.1, J65.1, TH1.2, TH2.2, TH3.2, TH4.2, TH5.2, TH6.2, TH7.2, TH8.2, TH9.2, TH10.2, TH11.2, TH12.2, TH13.2, TH14.2, TH15.2, TH16.2
unnamed: J34.1, TH1.1
unnamed: J35.1, TH2.1
unnamed: J36.1, TH3.1
unnamed: J37.1, TH4.1
unnamed: J38.1, TH5.1
unnamed: J39.1, TH6.1
unnamed: J40.1, TH7.1
unnamed: J41.1, TH8.1
unnamed: J42.1, TH9.1
unnamed: J43.1, TH10.1
unnamed: J44.1, TH11.1
unnamed: J45.1, TH12.1
unnamed: J46.1, TH13.1
unnamed: J47.1, TH14.1
unnamed: J48.1, TH15.1
unnamed: J49.1, TH16.1
